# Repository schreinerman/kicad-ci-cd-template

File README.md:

# kicad-ci-cd-template

CI/CD Pipeline Template for running KiCAD build processes

Run build.sh to...
```
./build.sh prepare      - Prepare for build
./build.sh schematic    - Build schematic artifacts only
./build.sh bom          - Build bill of materials artifacts only
./build.sh gerber       - Build gerber artifacts only
./build.sh cad          - Build 3D files only
./build.sh housing      - Build housing files only 
./build.sh docker       - build all using docker
./build.sh              - build all
```

Run Docker Compose...
```
docker compose up
```

# License
Created by Manuel Schreiner

Copyright © 2025 io-expert.com. All rights reserved.

Redistributions of source code must retain the above copyright notice, this condition and the following disclaimer.
This software is provided by the copyright holder and contributors "AS IS" and any warranties related to this software are DISCLAIMED. The copyright owner or contributors be NOT LIABLE for any damages caused by use of this software.

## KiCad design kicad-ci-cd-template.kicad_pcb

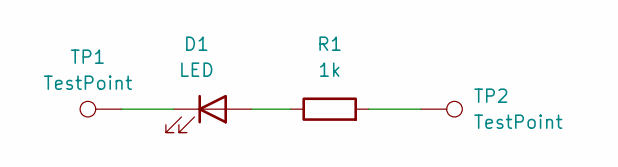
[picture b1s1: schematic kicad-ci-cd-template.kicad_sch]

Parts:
D1: LED; LED_D5.0mm
R1: 1k; R_Axial_DIN0204_L3.6mm_D1.6mm_P5.08mm_Horizontal
TP1, TP2: TestPoint; PinHeader_1x01_P2.54mm_Vertical

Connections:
unnamed: D1.2 (A), R1.1
unnamed: D1.1 (K), TP1.1
unnamed: R1.2, TP2.1

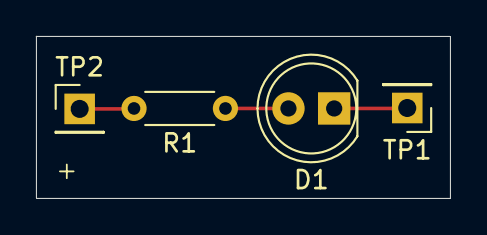
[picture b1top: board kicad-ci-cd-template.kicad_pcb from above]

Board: 2 copper layers, 23.0 x 9.0 mm, 4 parts (0 on the bottom side), 3 nets.

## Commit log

2025-04-23 fix path
2025-04-23 fixing syntax
2025-04-23 updating artefacts directory
2025-04-23 add support for runner on ubuntu-latest
2025-04-23 fixing build stage
2025-04-23 run with bash
2025-04-23 fix KICAD_CLI variable
2025-04-23 fix artifacts path
2025-04-23 adding artifacts
